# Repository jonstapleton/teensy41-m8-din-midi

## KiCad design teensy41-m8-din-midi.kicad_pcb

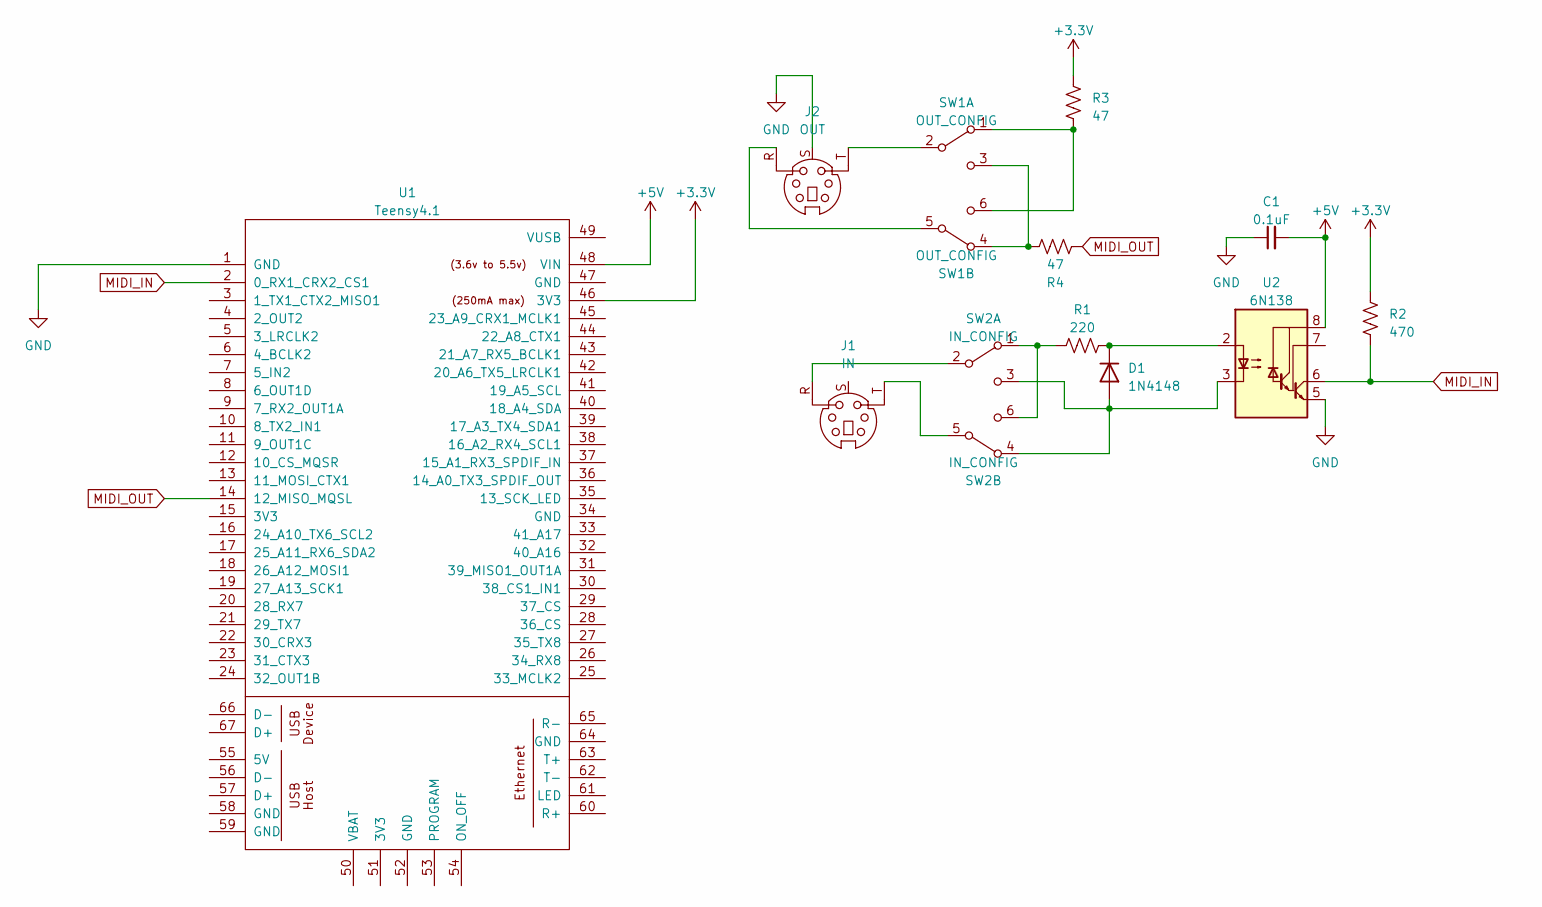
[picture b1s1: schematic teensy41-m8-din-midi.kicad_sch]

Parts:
C1: 0.1uF; C_Rect_L4.6mm_W2.0mm_P2.50mm_MKS02_FKP02
D1: 1N4148; D_DO-35_SOD27_P7.62mm_Horizontal
J1: IN; Jack_3.5mm_CUI_SJ-3523-SMT_Horizontal
J2: OUT; Jack_3.5mm_CUI_SJ-3523-SMT_Horizontal
R1: 220; R_Axial_DIN0204_L3.6mm_D1.6mm_P7.62mm_Horizontal
R2: 470; R_Axial_DIN0204_L3.6mm_D1.6mm_P7.62mm_Horizontal
R3, R4: 47; R_Axial_DIN0204_L3.6mm_D1.6mm_P7.62mm_Horizontal
SW1: OUT_CONFIG; SW_CuK_JS202011CQN_DPDT_Straight
SW2: IN_CONFIG; SW_CuK_JS202011CQN_DPDT_Straight
U1: Teensy4.1; Teensy41
U2: 6N138; DIP-8_W7.62mm_Socket

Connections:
+3.3V: R2.2, R3.2, U1.46 (3V3)
+5V: C1.2, U1.48 (VIN), U2.8 (VCC)
GND: C1.1, J2.S, U1.1 (GND), U2.5 (GND)
MIDI_IN: R2.1, U1.2 (0_RX1_CRX2_CS1), U2.6 (VO2)
MIDI_OUT: R4.1, U1.14 (12_MISO_MQSL)
unnamed: D1.2 (A), SW2.3 (C), SW2.4 (A), U2.3 (C2)
unnamed: D1.1 (K), R1.2, U2.2 (C1)
unnamed: R3.1, SW1.1 (A), SW1.6 (C)
unnamed: J2.T, SW1.2 (B)
unnamed: R4.2, SW1.3 (C), SW1.4 (A)
unnamed: J2.R, SW1.5 (B)
unnamed: R1.1, SW2.1 (A), SW2.6 (C)
unnamed: J1.R, SW2.2 (B)
unnamed: J1.T, SW2.5 (B)

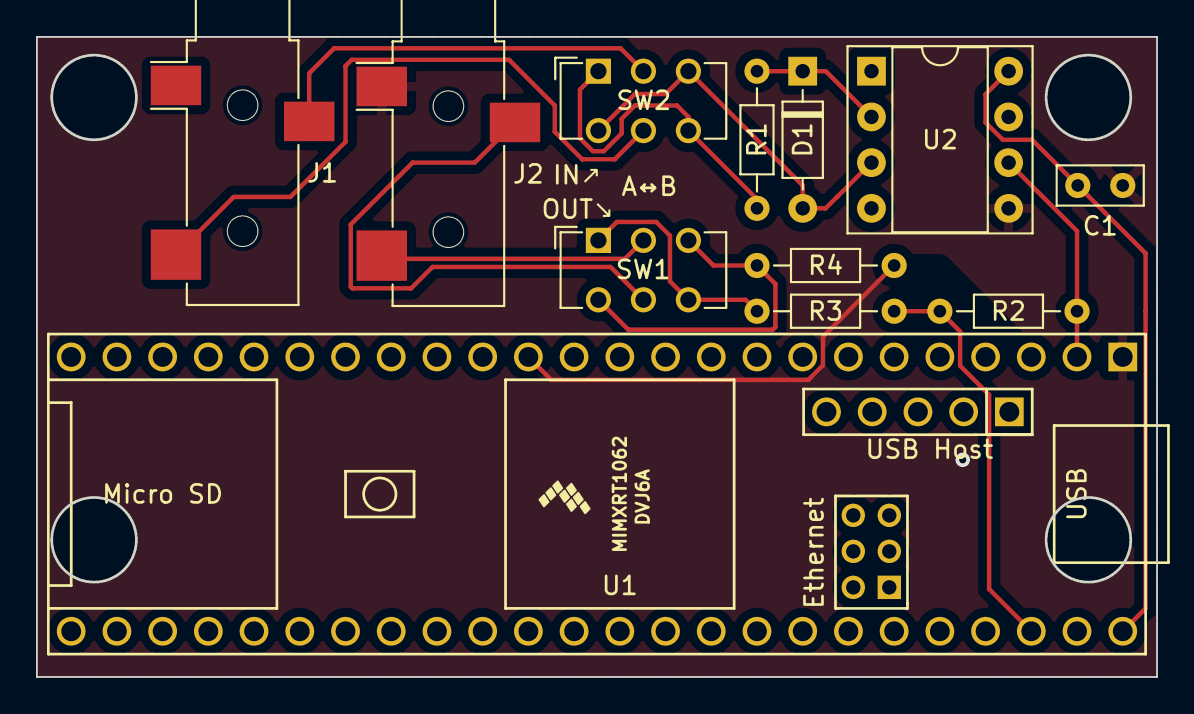
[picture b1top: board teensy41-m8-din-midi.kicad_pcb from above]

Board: 2 copper layers, 62.2 x 35.5 mm, 12 parts (0 on the bottom side), 14 nets.

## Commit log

2023-05-13 Fixed pin assignments
